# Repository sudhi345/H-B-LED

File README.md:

# H-B-LED
PCB for high brightness LED (Cree ® J Series™ 2835)

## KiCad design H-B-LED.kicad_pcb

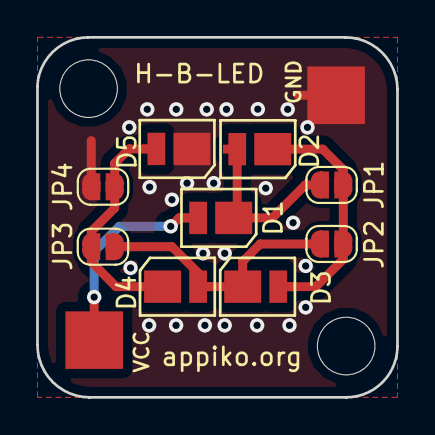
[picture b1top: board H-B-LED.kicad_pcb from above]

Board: 2 copper layers, 20.0 x 20.0 mm, 13 parts (0 on the bottom side), 6 nets.

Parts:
D1, D2, D3, D4, D5: LED; Cree_J_2835
H1, H2: MountingHole; MountingHole_3.2mm_M3_ISO7380
H3, H3#2: Vcc; POWER
JP1, JP2, JP3, JP4: Jumper; SolderJumper-2_P1.3mm_Open_RoundedPad1.0x1.5mm

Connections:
/C1A2: D1.1, D2.2, JP1.2
/C2A3: D2.1, D3.2, JP1.1, JP2.2
/C3A4: D3.1, D4.2, JP2.1, JP3.2
/C4A5: D4.1, D5.2, JP3.1, JP4.2
/GND: D5.1, H3#2.1, JP4.1
/VCC: D1.2, H3.1

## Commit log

2019-07-09 Upload files
2019-07-09 Added datasheet
